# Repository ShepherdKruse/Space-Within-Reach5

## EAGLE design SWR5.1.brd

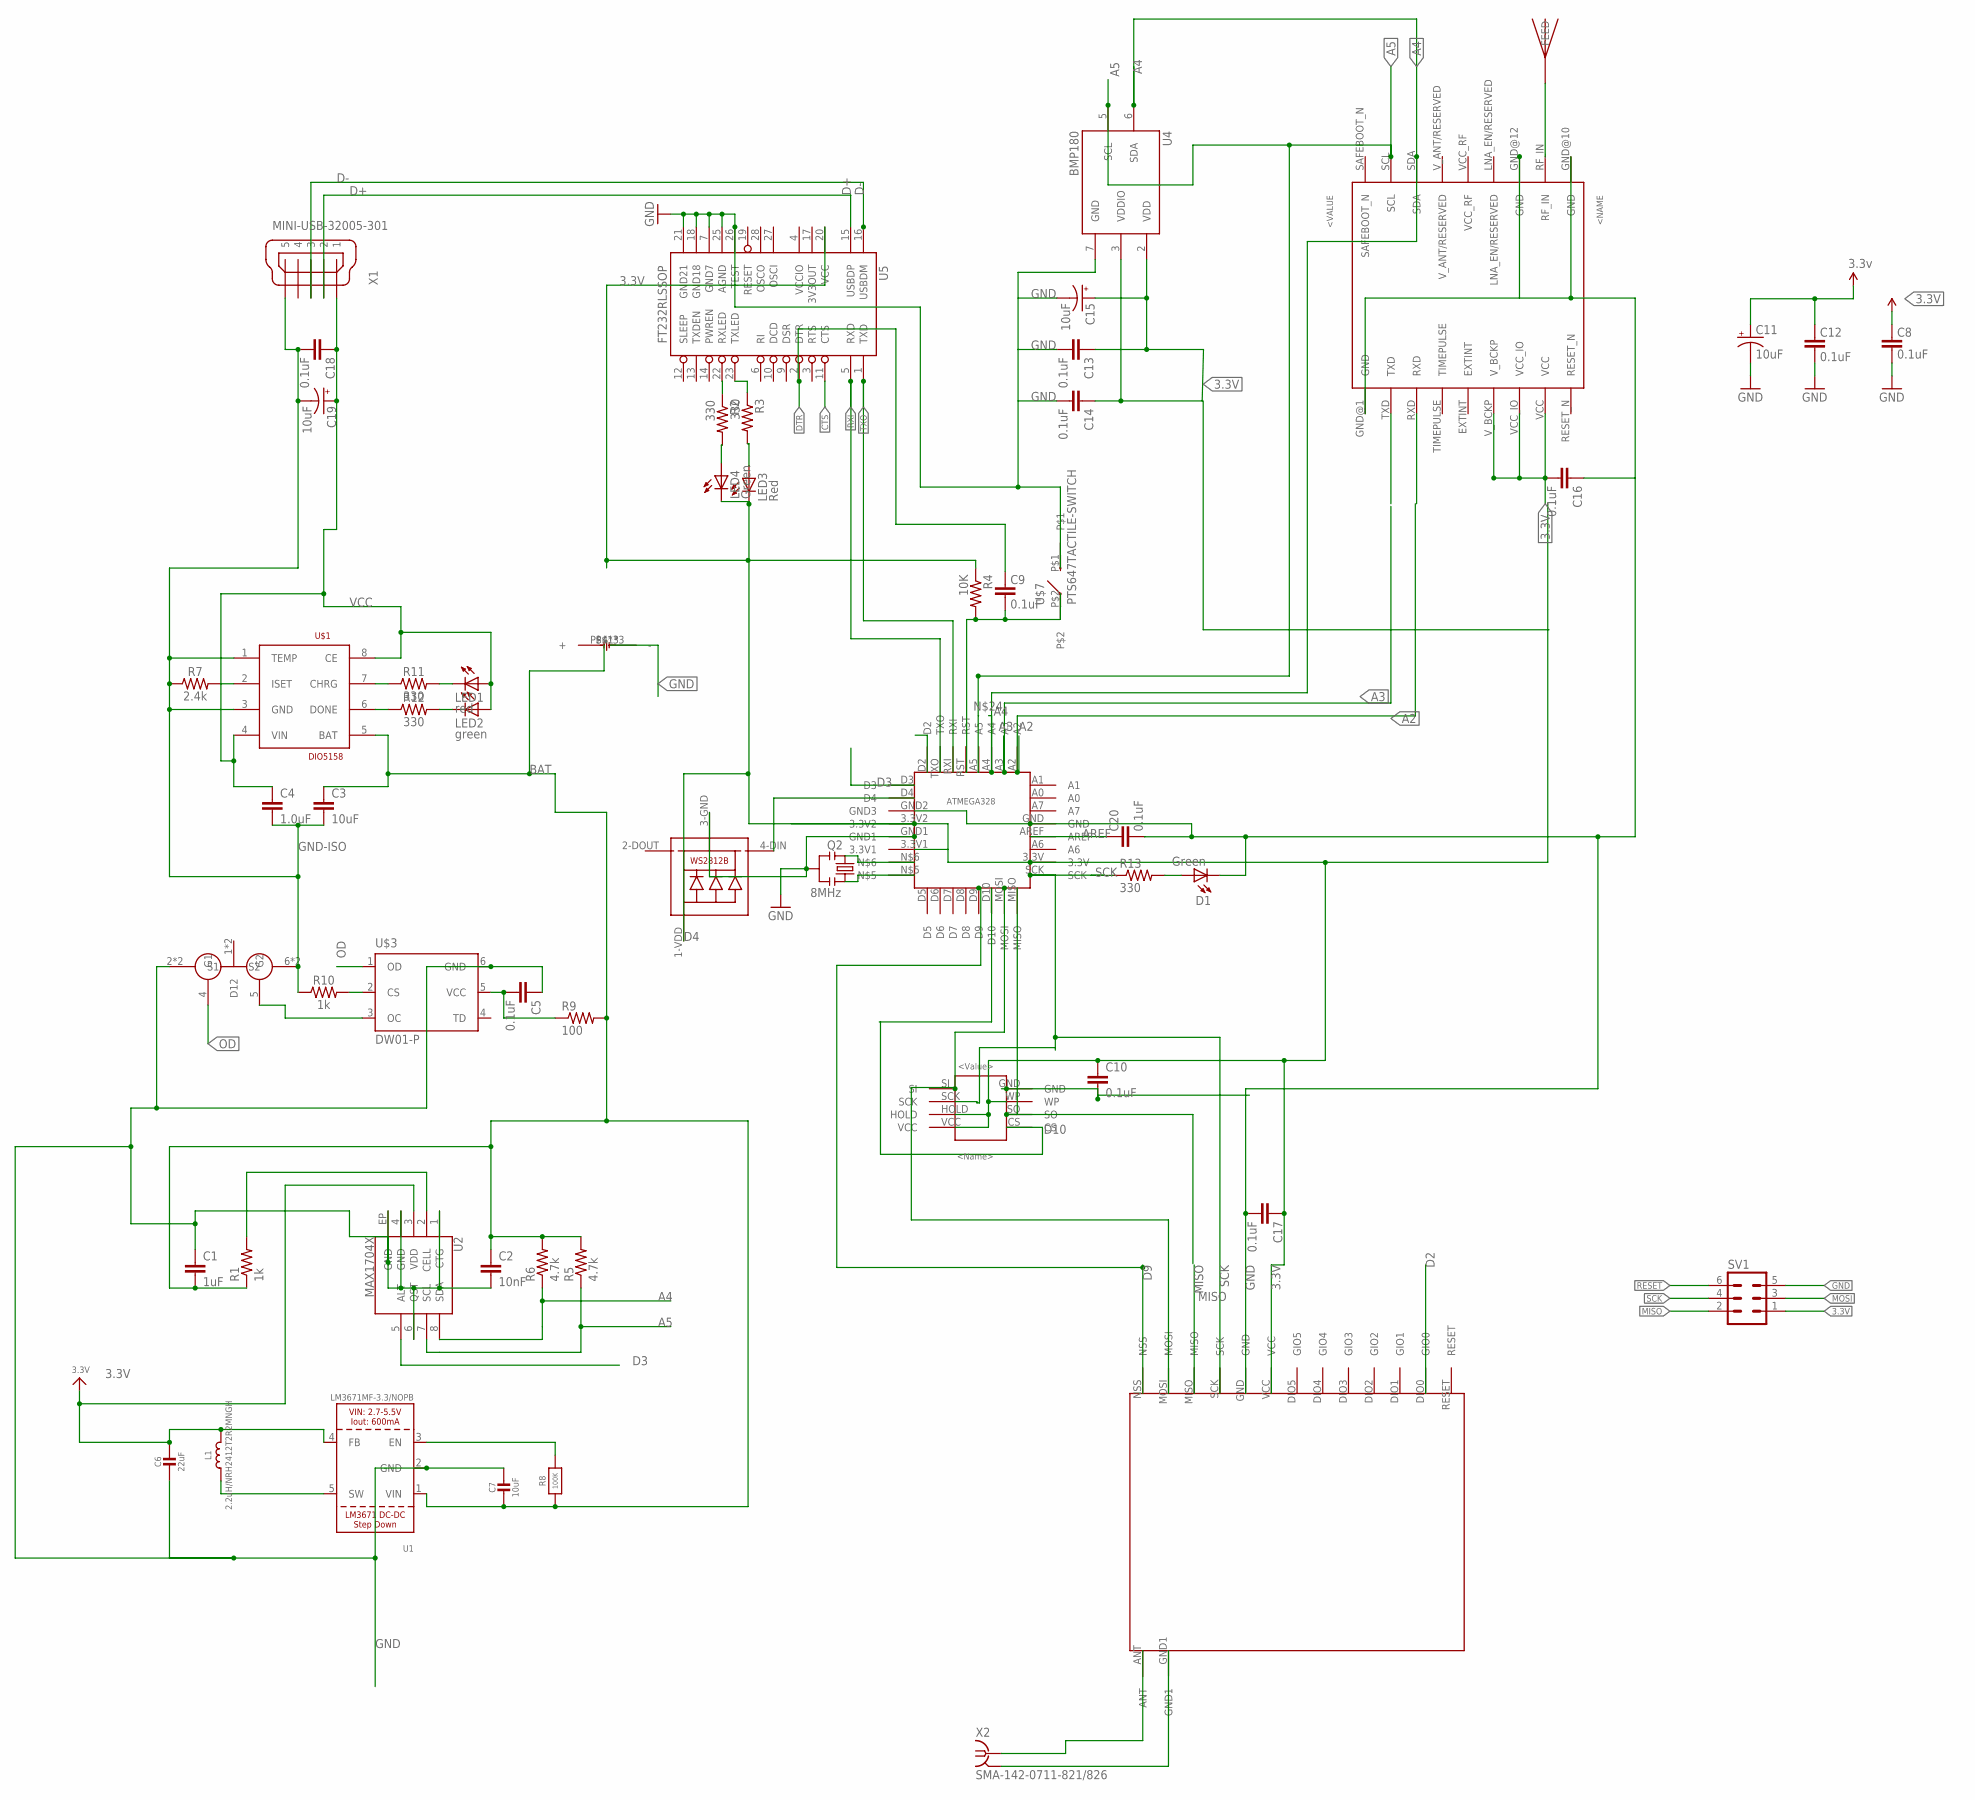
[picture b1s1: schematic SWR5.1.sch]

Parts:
C1: 1uF; 0402-CAP
C2: 10nF; 0402-CAP
C3: 10uF; 1206
C4: 1.0uF; 0603
C5: 0.1uF; 0603
C6: 22uF; 0805-NO
C7: 10uF; 0805-NO
C8, C9, C10, C12, C13, C14, C16, C17, C18, C20: 0.1uF; 0603-CAP
C11: 10uF; EIA3528
C15, C19: 10uF; EIA3216
D1: Green; 0603-LED-ALT1
GND-ISO: 18650BATT
L1: 2.2uH/NRH2412T2R2MNGH; INDUCTOR_TAIYOYUDEN_NRH2412T
LED1: red; CHIP-LED0805
LED2: green; CHIP-LED0805
LED3: Red; LED-0603
LED4: Green; LED-0603
LED5: WS2812B5050; WS2812B
LORATX: SX1272BETTER
Q2: 8MHz; RESONATOR-SMD-1:1
R1: 1k; 0402-RES
R2, R3, R13: 330; 0603-RES
R4: 10K; 0603-RES
R5, R6: 4.7k; 0402-RES
R7: 2.4k; 0603
R8: 100K; 0805-NO
R9: 100; 0603-RES
R10: 1k; 0603
R11, R12: 330; 0603
SV1: MA03-2
U1: LM3671MF-3.3/NOPB; SOT23-5
U2: MAX1704X; TDFN-8
U4: BMP180
U5: FT232RLSSOP; SSOP28DB
U$1: DIO5158; SOIC-8
U$2: AT25STORAGE
U$3: DW01-P; SOT23-6L
U$4: FS8205A; TSSOP8
U$5: ATMEGA328
U$7: PTS647TACTILE-SWITCH
U$8: AVA_JTI_ANTENNA-1575AT43A40
UBLX_MAX-M8Q: UBLXM8Q; UBLOXM8Q
X1: MINI-USB-32005-301; 32005-301
X2: SMA-142-0711-821/826; J502-ND-142-0711-821/826

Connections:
3.3V: C6.1, C8.2, C10.1, C11.A (+), C12.2, C13.1, C14.1, C15.A (+), C16.2, C17.1, L1.2, LED3.C, LED4.C, LED5.1-VDD (VDD), LORATX.VCC, R4.1, SV1.1, U1.4 (FB), U2.3 (VDD), U4.2 (VDD), U4.3 (VDDIO), U5.20 (VCC), U$2.HOLD, U$2.VCC, U$2.WP, U$5.3.3V, U$5.3.3V1, U$5.3.3V2, UBLX_MAX-M8Q.VCC, UBLX_MAX-M8Q.VCC_IO, UBLX_MAX-M8Q.V_BCKP
A2: U$5.A2, UBLX_MAX-M8Q.RXD
A3: U$5.A3, UBLX_MAX-M8Q.TXD
A4: R6.1, U2.8 (SDA), U4.6 (SDA), U$5.A4, UBLX_MAX-M8Q.SDA
A5: R5.1, U2.7 (SCL), U4.5 (SCL), U$5.A5, UBLX_MAX-M8Q.SCL
AREF: C20.2, U$5.AREF
BAT: C1.2, C2.1, C3.1, C7.2, GND-ISO.P$4 (+), GND-ISO.P$5 (+), GND-ISO.P$6 (+), R1.1, R5.2, R6.2, R8.1, R9.2, U1.1 (VIN), U$1.5 (BAT)
CELL: R1.2, U2.2 (CELL)
CHRG: R11.1, U$1.7 (CHRG)
CS: R10.2, U$3.2 (CS)
CTS: U5.11 (CTS)
D2: LORATX.DIO0 (GIO0), U$5.D2
D3: U2.5 (ALT), U$5.D3
D4: LED5.4-DIN (DI), U$5.D4
D9: LORATX.NSS, U$5.D9
D10: U$2.CS, U$5.D10
D+: U5.15 (USBDP), X1.2
D-: U5.16 (USBDM), X1.3
DONE: R12.1, U$1.6 (DONE)
DTR: C9.2, U5.2 (DTR)
EN: R8.2, U1.3 (EN)
GND: C1.1, C2.2, C5.1, C6.2, C7.1, C8.1, C10.2, C11.C (-), C12.1, C13.2, C14.2, C15.C (-), C16.1, C17.2, C20.1, D1.C, GND-ISO.P$1 (-), GND-ISO.P$2 (-), GND-ISO.P$3 (-), LED5.3-GND (GND), LORATX.GND, LORATX.GND1, Q2.2, SV1.5, U1.2 (GND), U2.1 (CTG), U2.4 (GND), U2.6 (QST), U2.EP (GND), U4.7 (GND), U5.7 (GND7), U5.18 (GND18), U5.21 (GND21), U5.25 (AGND), U5.26 (TEST), U$2.GND, U$3.6 (GND), U$4.2 (S1), U$4.3 (S1), U$5.GND, U$5.GND1, U$5.GND2 (GND3), U$7.P$1, UBLX_MAX-M8Q.GND@1 (GND), UBLX_MAX-M8Q.GND@10 (GND), UBLX_MAX-M8Q.GND@12 (GND), X2.G@1 (2), X2.G@2 (2), X2.G@3 (2), X2.G@4 (2)
GND-ISO: C3.2, C4.2, C18.2, C19.C (-), R7.1, R10.1, U$1.1 (TEMP), U$1.3 (GND), U$4.6 (S2), U$4.7 (S2), X1.5
ISET: R7.2, U$1.2 (ISET)
LED2: LED2.C, R12.2
MISO: LORATX.MISO, SV1.2, U$2.SO, U$5.MISO
MOSI: LORATX.MOSI, SV1.3, U$2.SI, U$5.MOSI
unnamed: C5.2, R9.1, U$3.5 (VCC)
unnamed: R3.1, U5.23 (TXLED)
unnamed: R2.1, U5.22 (RXLED)
unnamed: Q2.3, U$5.N$5
unnamed: LED1.C, R11.2
unnamed: Q2.1, U$5.N$6
unnamed: LED4.A, R2.2
unnamed: LORATX.ANT, X2.1
unnamed: LED3.A, R3.2
unnamed: D1.A, R13.2
OC: U$3.3 (OC), U$4.5 (G2)
OD: U$3.1 (OD), U$4.4 (G1)
RESET: C9.1, R4.2, SV1.6, U$5.RST, U$7.P$2
RF_IN: U$8.FEED, UBLX_MAX-M8Q.RF_IN
RXI: U5.5 (RXD), U$5.TXO
SCK: LORATX.SCK, R13.1, SV1.4, U$2.SCK, U$5.SCK
SW: L1.1, U1.5 (SW)
TXO: U5.1 (TXD), U$5.RXI
VCC: C4.1, C18.1, C19.A (+), LED1.A, LED2.A, U$1.4 (VIN), U$1.8 (CE), X1.1
VCCIO: U5.4 (VCCIO)

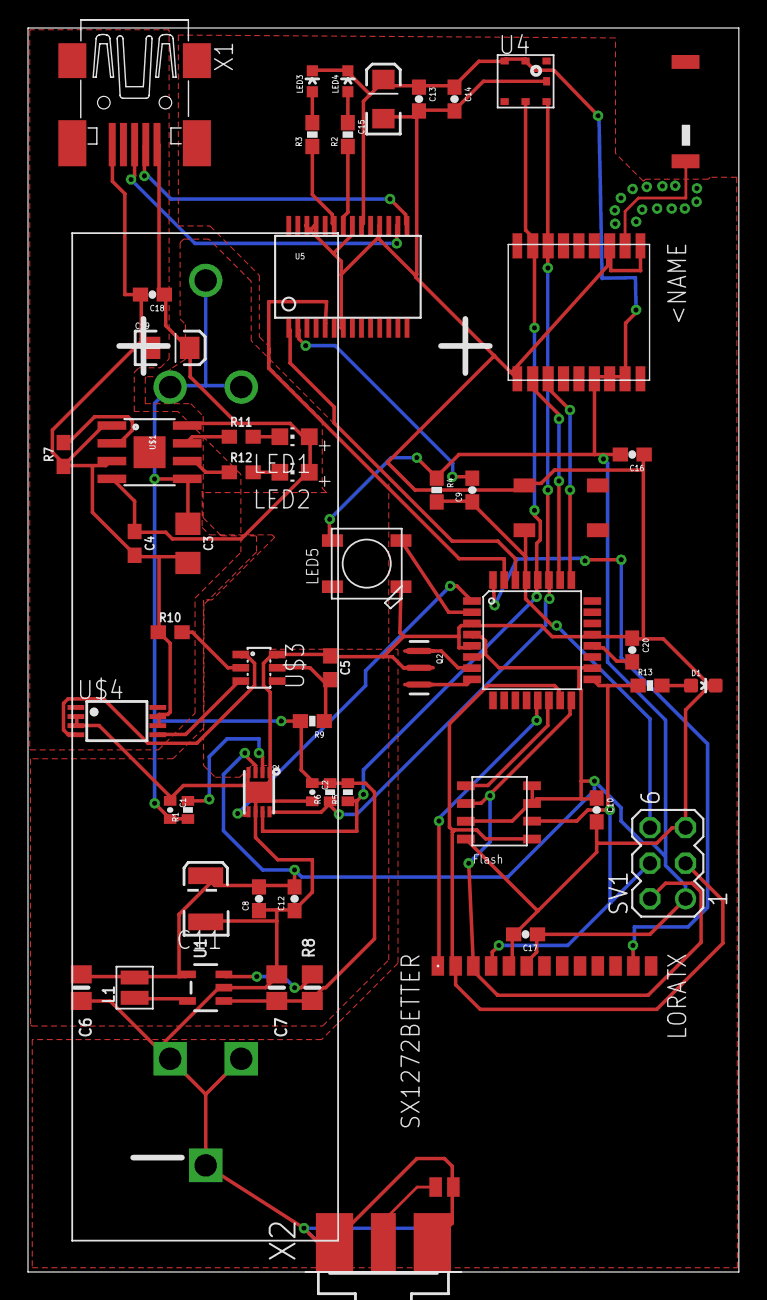
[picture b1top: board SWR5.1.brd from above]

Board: 2 copper layers, 50.8 x 88.9 mm, 58 parts (0 on the bottom side), 45 nets.

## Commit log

2019-02-19 All programs to be used
2019-05-28 Borad File
    Main Board file
2019-05-28 swr5.1
    Schematic for main board

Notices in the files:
parts and their libraries:
SparkFun-Capacitors: Licensing: Creative Commons ShareAlike 4.0 International - https://creativecommons.org/licenses/by-sa/4.0
microbuilder: This work is placed in the public domain, and may be freely used for commercial and non-commercial work with the following conditions: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
